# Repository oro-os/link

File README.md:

<div align="center">
	
</div>

# Oro Link

This is the Oro Link project, a set of custom PCBs, firmware, and server
infrastructure for the testing of the Oro Operating System via CI/CD pipelines.

The link is a physical board that interfaces with the ports and headers
of supported computers, devices, and boards, and runs firmware to obtain builds of
the Oro kernel and associated modules to send to the System Under Test (SUT)
for automated testing and reporting.

The Oro Link allows contributors to the Oro project direct access - via
pull requests - to test changes directly on real hardware
alongside emulated environments, allowing for changes to be tested
against niche or problematic hardware configurations.

## Project Layout

All PCBs are located in `pcb/`, where all of the server infrastructure and firmware for the PCBs
is located in `firmware/` since it's a workspace with some local dependencies (e.g. the protocol
spoken between the boards and the CI/CD daemon).

# License

<div align="center">
	
</div>

Part of the Oro Operating System project.

The Oro Link is released to the public, WARRANTY FREE
and provided AS IS. The Oro project and its contributors are NOT
responsible for any damages caused by the purchase, assembly, or operation
of the device, under any circumstances.

The Oro Link's PCB and associated custom footprints are released
under the [MIT License](LICENSE).

Unless otherwise specified, all Oro Link firmware (software code)
and all other materials are licensed under the same license.

Firmware dependencies are under their respective licenses.

The _Enter Command_ font used in part for text display is released CC-BY-4.0
by [Font End Dev (jeti)](https://fontenddev.com).

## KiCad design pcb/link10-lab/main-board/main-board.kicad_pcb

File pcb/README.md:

# Oro Link PCBs

The Oro Link PCBs are custom boards meant to interface with the
CI/CD daemon, which itself works with (at the moment, solely) GitHub
Actions runners that it manages.

These PCBs are open source and licensed under the license found in the
root of this repository.

All PCBs are designed in KiCad 7, with some technical sketches
designed in FreeCad.

There are some "legacy" PCBs here that haven't been converted to
self-standing projects (that use the `.lib/` folder). Further,
some of these PCBs are specific to individual rigs and may not
be interesting to most people.

## `link-rpi-base`

This is the base board for Raspberry Pi test rigs. It hosts
the microcontroller, network interface, etc. as well as a
board-to-board connector that interfaces with one of the
daughter boards (R-Pi version specific).

## `link-x86-obt`

> **NOTE:** This project file is a _legacy_ PCB that hasn't
> been converted to use the common components/footprints library
> in `.lib/`. You will be able to view the schematic and layout,
> but changes are more difficult to make and manage. Due to this,
> PRs that include changes to this PCB might take longer to merge.

This is the main board for testing x86/x86_64 machines using
the Oro Link CI/CD pipeline. Kernel builds are booted over PXE,
and communication is done primarily through the serial ports.

The board's form factor is designed to be mounted to the front
of an [Open Bench Table](https://openbenchtable.com/) - hence
`*-obt`.

As such, the board has two ethernet connections - one for communication
with the SUT, and the other for communication with the Link daemon.

Please see the [firmware directory](../firmware/link-firmware-x86)
for a block diagram and further explanations.

## `rj45-inverter-h410mb`

> **NOTE:** This is a rig-specific board that is likely uninteresting
> to you. It's meant to fit and cater to a very specific hardware
> configuration that most likely won't match yours. As such, this PCB
> is not required to operate a Link test rig, and probably won't
> be of use unless you match the test rig's build exactly.

> **NOTE:** This project file is a _legacy_ PCB that hasn't
> been converted to use the common components/footprints library
> in `.lib/`. You will be able to view the schematic and layout,
> but changes are more difficult to make and manage. Due to this,
> PRs that include changes to this PCB might take longer to merge.

This board has a board-mounted RJ-45 plug (_not_ socket - THT
mounted plugs were really tricky to find!) that is wired same-side
to an RJ-45 port. It's used on one of the x86 test rigs to keep the
left side of the OBT setup flush, without having an ethernet cable
poking out to the left and causing clearance issues.

## `vga-display-card-h410mb`

> **NOTE:** This is a rig-specific board that is likely uninteresting
> to you. It's meant to fit and cater to a very specific hardware
> configuration that most likely won't match yours. As such, this PCB
> is not required to operate a Link test rig, and probably won't
> be of use unless you match the test rig's build exactly.

> **NOTE:** This project file is a _legacy_ PCB that hasn't
> been converted to use the common components/footprints library
> in `.lib/`. You will be able to view the schematic and layout,
> but changes are more difficult to make and manage. Due to this,
> PRs that include changes to this PCB might take longer to merge.

This board provides power to a [VGA display](https://www.amazon.de/-/en/gp/product/B09ZDK5DMT/ref=ppx_yo_dt_b_search_asin_title?ie=UTF8&psc=1) via a PCIe x1
port on the motherboard. It also doubles as a VGA port mount
for the graphics card (which uses a cable to interface between the
card and the port), which further allows the left side of the OBT
to remain flush.

If you're interested in using the VGA display linked above, I
recommend to take it apart, desolder the transducer (beeper)
in the top corner of the board, and replace it with a resistor,
lest you go insane.

# Making a new board

If you want to add a project here, you'll need to do a few things:

1. Make the folder here. Use kebab-case, such as `link-rpi-2` instead of
   `LinkRpi2`.
2. Open KiCad and create the project in the folder. Uncheck the box that
   asks if you want to create a project folder. Preferably, name the project
   using TitleCase, such as `LinkRpi2`.
3. From any **non-legacy** project (see the above list), copy `fp-lib-table`
   and `sym-lib-table` into the new project's directory. **Restart KiCad.**
4. In both the schematic and the PCB layout, go to _File > Page Setup..._
   and change the worksheet to `${KIPRJMOD}/../.lib/Oro.kicad_wks`.
5. If you're using common sheets to re-use some of the modular schematics
   from other boards, **always use relative paths**
   (e.g. `${KIPRJMOD}/../.lib/<something>`).

If you're adding a component, it is **highly** recommended to add it from
[Ultra Librarian](https://ultralibrarian.com).

Symbols and footprints must be added to `.lib/Oro.kicad_sym` and `.lib/Oro.pretty/`,
respectively. STEP models should be placed in `.lib/step` and properly linked up
from within the footprint (usually requires manually editing the footprint after
loading it into `Oro.pretty/`).

Further, make sure to update the footprint ID in the symbol after moving it into the
Oro library.

Most importantly, **you must make sure all common fields are populated and accurate**.
These are fields found on other symbols, the names of which must match **exactly**.
For example, Mouser ID, Mfr. ID, etc.

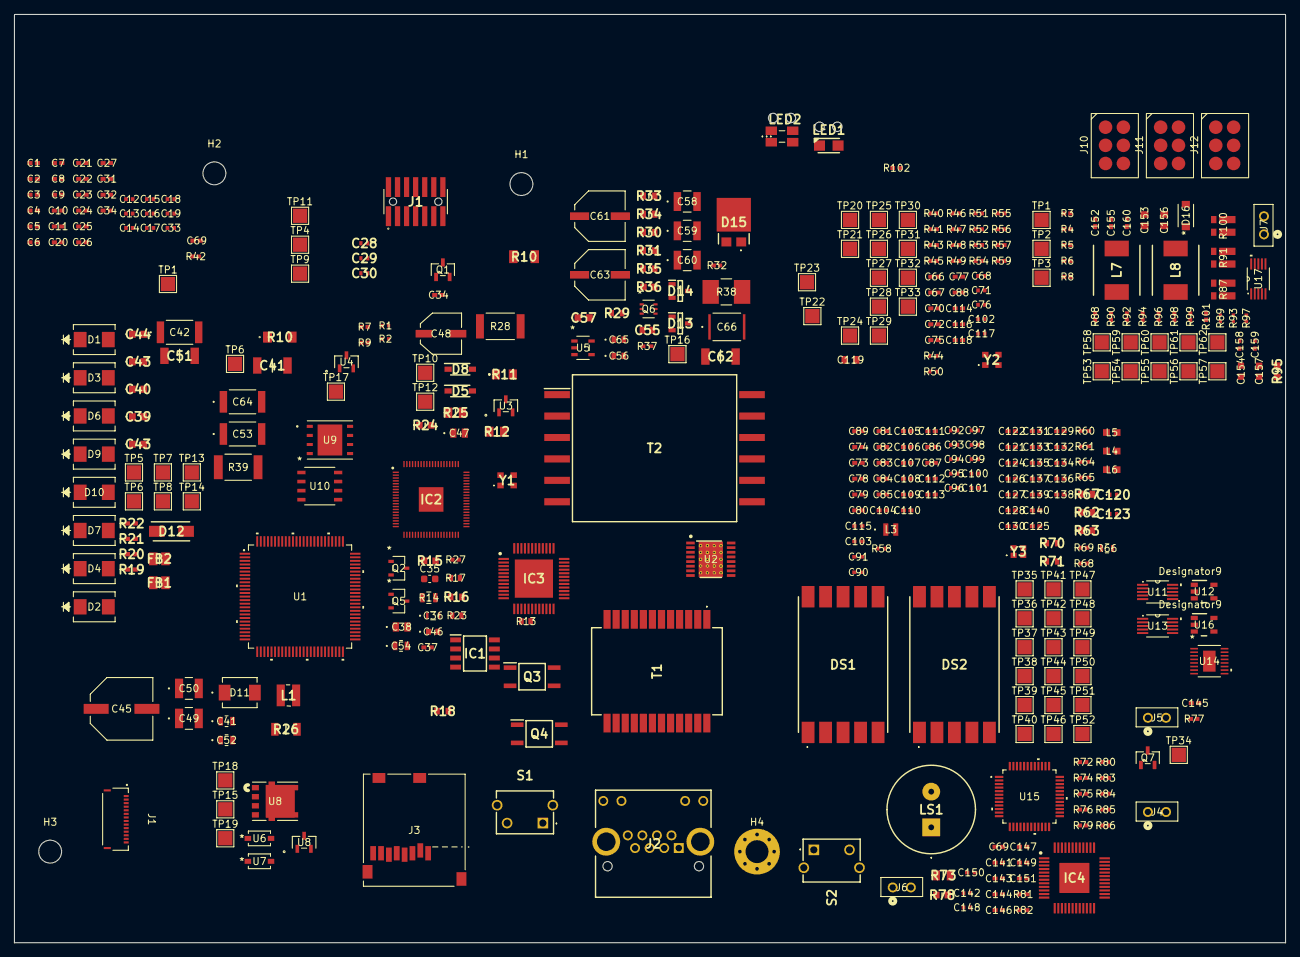
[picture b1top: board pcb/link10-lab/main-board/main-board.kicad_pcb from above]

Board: 2 copper layers, 178.0 x 130.0 mm, 415 parts (0 on the bottom side), 212 nets, no tracks yet.

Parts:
C1, C2, C3: 2.2u; OP_0001G
C4, C5, C6, C7, C8, C9, C10, C11, C32, C34, C34#2, C37, C67, C69, C69#2, C70, C73, C74, C75, C78, C79, C80, C81, C82, C83, C84, C85, C86, C87, C88, C89, C116, C121, C122, C124, C125, C127, C128, C131, C132, C133, C134, C136, C137, C138, C139, C140, C141, C144, C145, C146, C147, C151, C152, C155, C160: 0.1u; OP_0001Y
C12, C13, C14, C15, C16, C17, C18, C19, C33, C68, C71, C76, C92, C93, C94, C95, C96, C97, C98, C99, C100, C101, C102, C117, C142, C148: 0.01u; OP_0000F
C20, C21, C22, C23, C24, C25, C26, C27, C31, C66, C72, C77, C104, C105, C106, C107, C108, C109, C110, C111, C112, C113, C114, C118, C126, C129, C130, C135, C143, C149: 1u; OP_0001R
C28, C29, C30, C90, C91, C103, C115, C150, C158, C159: 4.7u; OP_00014
C35: DNP; C_0603_1608Metric
C36: 0.022uF 50V; OP_00069
C38: 1uF; OP_0005T
C39, C40, C43#2, C44: 10nF 150V; OP_0005C
C41: 1000pF >=2kV; OP_0000R
C41#2, C52, C54: 0.1uF 100V; OP_0005M
C42, C64: 1000pF Y2; OP_0006V
C43: 10nF >=150V; OP_0005C
C45: 47uF 63V; OP_0005N
C46: 330pF; OP_00068
C47: 1uF 25V; OP_0005T
C48: 22uF 25V; OP_0005V
C49, C50: 1uF 100V X7R 1210; OP_0005L
C51: 1000pF 2kV; OP_0000R
C53: 2200pF Y2; OP_0006U
C55: 470pF; OP_0006Q
C56, C65: 1uF; OP_00001
C57: 0.01u; OP_0005C
C58, C59, C60: 47uF; OP_0006G
C61, C63: 330uF; OP_0006H
C62: 1000pF; OP_0000R
C66#2: 2200pF 2kV; OP_0006T
C119, C153, C156: 10u; OP_0001M
C120, C123: 12pF 1% C0G; OP_00071
C154, C157: 22u; OP_00015
D1, D2, D3, D4, D6, D7, D9, D10: B2100-13-F; OP_0005E
D5, D8: 1N4148W; OP_0005S
D11: MURS120T3G; OP_0005P
D12: 824500581 OR SMAJ58A; OP_0005G
D13, D14: BAT54; OP_0006I
D15: SS8P4C-M3_87A; OP_0006E
D16: SMF6V0A-M3-08; OP_0003V
DS1, DS2: HDSM-531W; OP_00077
FB1, FB2: 500R >=1.5A; OP_0005F
H1, H2, H3: MountingHole; MountingHole_3.2mm_M3
H4: MountingHole_Pad; MountingHole_3.2mm_M3_Pad_Via
H5, H6: SLP3-200-100-F; OP_0007E
IC1: SI4848DY-T1-E3; OP_0005R
IC2: SC1510-A4; OP_00050
IC3: W6300-L; OP_00056
IC4: IS31FL3236A-TQLS4-TR; OP_0001Q
J1: 5034801400; OP_00052
J1#2: FTSH-107-01-L-DV-K-A-TR; OP_0005A
J2: 1149867; OP_00053
J3: MEM2061-01-188-00-A; OP_0001X
J4, J5, J6, J7: TSW-102-07-T-S; OP_00079
J10, J11, J12: CPG-81-TH-B-Pads; CPG-81-TH-B-Landing
L1: LPS3015-332MRC; OP_0005I
L3: AOTA-B201610S3R3-101-T; OP_00073
L4, L5, L6: BLM18PG221SN1D; OP_0000Y
L7, L8: 2.2u; OP_0007C
LED1: CLM3C-WKW-CXAYA453; OP_00016
LED2: 150120M173000; OP_00006
LS1: CPT-1206-3TH-T; OP_00078
Q1, Q7: PMV20ENR; OP_0001Z
Q2, Q5: SI2304DDS-T1-BE3; OP_00063
Q3, Q4: HCPL-181-06AE; OP_00062
Q6: 2N7002DW; OP_0006D
R1, R2, R81, R82, R102: 4.7K; OP_0001C
R3, R4, R5, R6, R7, R8, R9, R27, R32, R40, R41, R42, R43, R45, R46, R47, R48, R49, R51, R52, R53, R54, R55, R56, R57, R59, R68, R69, R72, R74, R75, R76, R77, R79, R80, R83, R84, R85, R86, R88, R90, R92, R94, R96, R98, R99, R101: 10K; OP_00021
R10: ~1M ANTI-SURGE; OP_0005D
R10#2: 24.9K 1% 1/4W 150V; OP_0005H
R11: 63R4 1/10W 1%; OP_0005W
R12: 34K 1%; OP_0005X
R13: 3.65K 1%; OP_0006A
R14: 1K; OP_0003D
R15, R78, R95: 100K; OP_00066
R16: 33.2K 1%; OP_00065
R17: 549K 1%; OP_00064
R18: 475K 1/16W 1%; OP_0005Q
R19, R20, R21, R22: 75R 1%; OP_0002Z
R23: 332R; OP_00067
R24: 43R2 1%; OP_0005Y
R25: 10R 0805; OP_0005U
R26: 15K 0.25W; OP_0005O
R28: 0.1R 1% 1/2W; OP_00060
R29, R70, R71: 604R; OP_0006K
R30: 4R7; OP_0006O
R31: 4.99K; OP_0006P
R33: 41.2K; OP_0006J
R34: 13.7K; OP_0006M
R35: 20K; OP_0006R
R36: 30.1K; OP_0006S
R37, R60, R61, R64, R65: 49R9; OP_00023
R38: 10R 1W; OP_0006N
R39: 1-2.2M 2kV; OP_0006W
R44, R50: 22R-33R; OP_00022
R58: 33R; OP_00022
R62: 1M; OP_00072
R63: 0R; OP_0004Y
R66: 12K 1%; OP_0006Y
R67: 300R 1%; OP_0006Z
R73: 470R; OP_00031
R87, R91, R100: 2m; OP_0002G
R89, R93: 45.3K; OP_0007A
R97: 249R; OP_0007B
S1, S2: MJTP1129B; OP_0005B
T1: 749022011; OP_00058
T2: NA5730-ALD; OP_0005J
TP1: STM_BOOT1; TestPoint_Pad_2.0x2.0mm
TP1#2: CHASSIS; TestPoint_Pad_2.0x2.0mm
TP2: STM_BOOT0; TestPoint_Pad_2.0x2.0mm
TP3: STM_NRST; TestPoint_Pad_2.0x2.0mm
TP4: POE_CS; TestPoint_Pad_2.0x2.0mm
TP5: PAIR12; TestPoint_Pad_2.0x2.0mm
TP6: GND; TestPoint_Pad_2.0x2.0mm
TP6#2: PAIR36; TestPoint_Pad_2.0x2.0mm
TP7: PAIR45; TestPoint_Pad_2.0x2.0mm
TP8: PAIR78; TestPoint_Pad_2.0x2.0mm
TP9: POE_GATE; TestPoint_Pad_2.0x2.0mm
TP10: POE_VC; TestPoint_Pad_2.0x2.0mm
TP11: POE_PRIM_SWITCH_WAV; TestPoint_Pad_2.0x2.0mm
TP12: POE_AGND; TestPoint_Pad_2.0x2.0mm
TP13: POE_VDD; TestPoint_Pad_2.0x2.0mm
TP14: POE_VSS; TestPoint_Pad_2.0x2.0mm
TP15: POE_SDRN; TestPoint_Pad_2.0x2.0mm
TP16: POE_LOOP; TestPoint_Pad_2.0x2.0mm
TP17: POE_CHASSIS; TestPoint_Pad_2.0x2.0mm
TP18: POE_+5V; TestPoint_Pad_2.0x2.0mm
TP19: POE_GND; TestPoint_Pad_2.0x2.0mm
TP20: RP_QSS0; TestPoint_Pad_2.0x2.0mm
TP21: RP_QD1; TestPoint_Pad_2.0x2.0mm
TP22: RP_QD2; TestPoint_Pad_2.0x2.0mm
TP23: RP_QD0; TestPoint_Pad_2.0x2.0mm
TP24: RP_QCLK; TestPoint_Pad_2.0x2.0mm
TP25: RP_QD3; TestPoint_Pad_2.0x2.0mm
TP26: RP_QSS1; TestPoint_Pad_2.0x2.0mm
TP27: SD_CLK; TestPoint_Pad_2.0x2.0mm
TP28: SD_CMD; TestPoint_Pad_2.0x2.0mm
TP29: SD_DAT0; TestPoint_Pad_2.0x2.0mm
TP30: SD_DAT1; TestPoint_Pad_2.0x2.0mm
TP31: SD_DAT2; TestPoint_Pad_2.0x2.0mm
TP32: SD_DAT3; TestPoint_Pad_2.0x2.0mm
TP33: SD_DETECT; TestPoint_Pad_2.0x2.0mm
TP34: RP_NRST; TestPoint_Pad_2.0x2.0mm
TP35: BB_SCL; TestPoint_Pad_2.0x2.0mm
TP36: BB_SDA; TestPoint_Pad_2.0x2.0mm
TP37: DGT_~{RST}; TestPoint_Pad_2.0x2.0mm
TP38: DGT_~{SENSE}; TestPoint_Pad_2.0x2.0mm
TP39: BB_STM_~{INT}; TestPoint_Pad_2.0x2.0mm
TP40: BB_~{RST}; TestPoint_Pad_2.0x2.0mm
TP41: BB_SYS_~{RST}; TestPoint_Pad_2.0x2.0mm
TP42: BB_SPK; TestPoint_Pad_2.0x2.0mm
TP43: DGT_E0; TestPoint_Pad_2.0x2.0mm
TP44: DGT_E1; TestPoint_Pad_2.0x2.0mm
TP45: DGT_E2; TestPoint_Pad_2.0x2.0mm
TP46: DGT_E3; TestPoint_Pad_2.0x2.0mm
TP47: RP_E0; TestPoint_Pad_2.0x2.0mm
TP48: RP_E1; TestPoint_Pad_2.0x2.0mm
TP49: RP_E2; TestPoint_Pad_2.0x2.0mm
TP50: RP_E3; TestPoint_Pad_2.0x2.0mm
TP51: BB_LEDCTL_EN; TestPoint_Pad_2.0x2.0mm
TP52: MASTER_LIGHT_EN; TestPoint_Pad_2.0x2.0mm
TP53: BB_PWR_WARN; TestPoint_Pad_2.0x2.0mm
TP54: MASTER_PWR_WARN; TestPoint_Pad_2.0x2.0mm
TP55: STM_PWR_EN; TestPoint_Pad_2.0x2.0mm
TP56: DGT_PWR_EN; TestPoint_Pad_2.0x2.0mm
TP57: DGT_PWR_ALARM; TestPoint_Pad_2.0x2.0mm
TP58: DGT_PWR_WARN; TestPoint_Pad_2.0x2.0mm
TP59: 5V_BASE; TestPoint_Pad_2.0x2.0mm
TP60: 3V3_BASE; TestPoint_Pad_2.0x2.0mm
TP61: 3V3_STM; TestPoint_Pad_2.0x2.0mm
TP62: 5V_DGT; TestPoint_Pad_2.0x2.0mm
U1: STM32F479VGT6; OP_00028
U2: TPS23751PWP; OP_00057
U3, U4, U8: MMBT3906LT1G; OP_0005Z
U5: TLV431ASNT1G; OP_0006L
U6, U7: MBR0530T1G; OP_0006B
U8#2: NTMFS4C55NT1G; OP_0006C
U9: W25Q128JVPIM; OP_00054
U10: APS6404L-3SQR-SN; OP_00055
U11, U13, U17: INA226AIDGSR; OP_0001O
U12, U16: TLV62569DBVR; OP_00075
U14: LTC4415EMSE-PBF; OP_0004S
U15: STM32C031C4T6; OP_00076
Y1, Y2: ECS-2520SMV-240-FP-TR; OP_0001E
Y3: 25MHz CL=10pF; OP_00070

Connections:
+3V3_BASE: C144.2, C147.1, C148.1, C149.1, C150.1, C152.1, C154.1, C155.1, C160.1, L7.2, R72.2, R76.2, R79.1, R81.1, R82.1, R83.2, R84.2, R88.2, R89.1, R92.2, R96.2, R98.2, R99.2, R101.2, TP60.1 (1_1), U11.6 (VS), U13.2 (A0), U13.6 (VS), U15.5 (VREF+), U15.6 (VDD/VDDA), U17.1 (A1), U17.6 (VS)
+3V3_STM: C4.1, C5.1, C6.1, C7.1, C8.1, C9.1, C10.1, C11.1, C12.1, C13.1, C14.1, C15.1, C16.1, C17.1, C18.1, C19.1, C20.1, C21.1, C22.1, C23.1, C24.1, C25.1, C26.1, C27.1, C28.1, C29.1, C30.1, C31.2, C32.2, C33.2, C66.2, C67.2, C68.2, C70.1, C71.1, C72.1, C75.1, C76.1, C77.1, C78.1, C79.1, C80.1, C81.1, C82.1, C83.1, C84.1, C85.1, C86.1, C87.1, C88.1, C92.1, C93.1, C94.1, C95.1, C96.1, C97.1, C98.1, C99.1, C100.1, C101.1, C102.1, C103.2, C104.1, C105.1, C106.1, C107.1, C108.1, C109.1, C110.1, C111.1, C112.1, C113.1, C114.1, C116.1, C117.1, C118.1, C119.1, C126.2, C127.2, C128.2, C157.1, IC2.5 (IOVDD_1), IC2.15 (IOVDD_2), IC2.24 (IOVDD_3), IC2.29 (IOVDD_4), IC2.41 (IOVDD_5), IC2.50 (IOVDD_6), IC2.59 (ADC_AVDD), IC2.60 (IOVDD_7), IC2.64 (VREG_VIN), IC2.68 (USB_OTP_VDD), IC2.69 (QSPI_IOVDD), IC2.76 (IOVDD_8), IC3.10 (3V3D_1), IC3.24 (3V3D_2), IC3.36 (3V3D_3), J3.P4 (VDD), L5.2, L8.2, R1.1, R2.1, R3.2, R5.2, R6.2, R7.2, R9.2, R40.2, R41.2, R42.2, R43.1, R45.1, R46.1, R47.1, R48.1, R49.1, R51.2, R52.2, R53.2, R54.2, R55.2, R56.2, R57.2, R58.1, R59.2, R68.2, R70.2, R71.2, R77.2, R86.1, R93.1, TP61.1 (1_1), U1.3 (VBAT), U1.8 (VDD), U1.17 (VREF+), U1.18 (VDDA), U1.24 (VDD), U1.45 (VDD), U1.55 (VDDDSI), U1.65 (VDDUSB), U1.77 (VDD), U1.100 (VDD), U9.8 (VCC), U10.8 (VDD), Y1.4 (VDD), Y2.4 (VDD)
+5V: C63.1, C65.1, C158.1, D16.1, LED1.1 (A), R35.2, R36.2, R37.1, R87.1, R91.1, TP18.1 (1_1), U14.1 (IN1), U14.2 (IN1), U14.6 (*EN2)
+5V_BASE: C69#2.1, C142.1, C143.1, C153.1, DS1.3 (COMMON_ANODE_1), DS1.8 (COMMON_ANODE_2), DS2.3 (COMMON_ANODE_1), DS2.8 (COMMON_ANODE_2), IC4.41 (VCC), LED2.2 (A_G), R75.1, R87.4, TP59.1 (1_1), U11.8 (VBUS), U16.1 (EN), U16.4 (VIN)
+5V_DGT: R100.4, TP62.1 (1_1), U17.8 (VBUS)
/Baseboard/BB_PWR_WARN: R88.1, TP53.1 (1_1), U11.3 (ALERT), U15.8 (PF0-OSC_IN)
/Baseboard/DGT_ERR.E0: TP43.1 (1_1), U15.20 (PB1)
/Baseboard/DGT_ERR.E1: TP44.1 (1_1), U15.21 (PB2)
/Baseboard/DGT_ERR.E2: TP45.1 (1_1), U15.22 (PB10)
/Baseboard/DGT_ERR.E3: TP46.1 (1_1), U15.23 (PB11)
/Baseboard/DGT_PWR_ALARM: R99.1, TP57.1 (1_1), U14.13 (*WARN1), U15.29 (PA9)
/Baseboard/DGT_PWR_EN: R98.1, TP56.1 (1_1), U14.3 (EN1), U15.28 (PA8)
/Baseboard/DGT_PWR_WARN: R101.1, TP58.1 (1_1), U15.31 (PC7), U17.3 (ALERT)
/Baseboard/DGT_~RST: R78.2, TP37.1 (1_1), U15.27 (PB15)
/Baseboard/DGT_~SENSE: R83.1, TP38.1 (1_1), U15.37 (PA15)
/Baseboard/ERR_B: IC4.34 (OUT32), LED2.1 (K_B)
/Baseboard/ERR_G: IC4.35 (OUT33), LED2.3 (K_G)
/Baseboard/ERR_R: IC4.36 (OUT34), LED2.4 (K_R)
/Baseboard/I2C1.SCL: IC4.46 (SCL), R82.2, TP35.1 (1_1), U11.5 (SCL), U13.5 (SCL), U15.47 (PB8), U17.5 (SCL)
/Baseboard/I2C1.SDA: IC4.45 (SDA), R81.2, TP36.1 (1_1), U11.4 (SDA), U13.4 (SDA), U15.48 (PB9), U17.4 (SDA)
/Baseboard/LEDCTL_EN: IC4.39 (SDB), R74.1, TP51.1 (1_1), U15.4 (PF3)
/Baseboard/MASTER_LIGHT_EN: TP52.1 (1_1), U15.46 (PB7)
/Baseboard/MASTER_PWR_EN: J7.1, R95.1, TP55.1 (1_1), U12.1 (EN), U15.40 (PD2)
/Baseboard/MASTER_PWR_WARN: R92.1, TP54.1 (1_1), U13.3 (ALERT), U15.26 (PB14)
/Baseboard/O10: DS2.1 (CATHODE_E), IC4.9 (OUT10)
/Baseboard/O11: DS2.2 (CATHODE_D), IC4.10 (OUT11)
/Baseboard/O12: DS2.4 (CATHODE_C), IC4.11 (OUT12)
/Baseboard/O13: DS2.6 (CATHODE_B), IC4.12 (OUT13)
/Baseboard/O14: DS2.7 (CATHODE_A), IC4.13 (OUT14)
/Baseboard/O15: DS2.9 (CATHODE_F), IC4.14 (OUT15)
/Baseboard/O16: DS2.10 (CATHODE_G), IC4.15 (OUT16)
/Baseboard/O17: DS1.1 (CATHODE_E), IC4.16 (OUT17)
/Baseboard/O18: DS1.2 (CATHODE_D), IC4.17 (OUT18)
/Baseboard/O19: DS1.4 (CATHODE_C), IC4.20 (OUT19)
/Baseboard/O20: DS1.10 (CATHODE_G), IC4.21 (OUT20)
/Baseboard/O21: DS1.9 (CATHODE_F), IC4.22 (OUT21)
/Baseboard/O22: DS1.7 (CATHODE_A), IC4.23 (OUT22)
/Baseboard/O23: DS1.6 (CATHODE_B), IC4.24 (OUT23)
/Baseboard/RP_ERR.E0: IC2.40 (GPIO32), TP47.1 (1_1), U15.42 (PB3)
/Baseboard/RP_ERR.E1: IC2.39 (GPIO31), TP48.1 (1_1), U15.43 (PB4)
/Baseboard/RP_ERR.E2: IC2.38 (GPIO30), TP49.1 (1_1), U15.44 (PB5)
/Baseboard/RP_ERR.E3: IC2.37 (GPIO29), TP50.1 (1_1), U15.45 (PB6)
/Baseboard/RP_RST: Q7.1 (G), R77.1, U15.32 (PA10)
/Baseboard/SPI1.CLK: U1.37 (PE12), U15.16 (PA5)
/Baseboard/SPI1.MISO: U1.38 (PE13), U15.17 (PA6)
/Baseboard/SPI1.MOSI: U1.39 (PE14), U15.18 (PA7)
/Baseboard/SPI_~CS: R79.2, U15.19 (PB0)
/Baseboard/STM32_RST: Q1.1 (G), R9.1, U15.30 (PC6)
/Baseboard/STM32_~INT: R84.1, TP39.1 (1_1), U15.38 (PD0)
/Baseboard/~RST: C146.2, R76.1, TP40.1 (1_1), U15.10 (PF2-NRST)
/Bridge (RP) + SD/+1V1: C73.2, C74.2, C89.2, C90.2, C91.2, IC2.10 (DVDD_1), IC2.32 (DVDD_2), IC2.51 (DVDD_3), IC2.65 (VREG_FB), L3.1 (-)
/Bridge (RP) + SD/+3V3A: C115.2, IC2.61 (VREG_AVDD), R58.2
/Bridge (RP) + SD/AGND: C69.1, S1.2 (NO)
/Bridge (RP) + SD/DGT_SDIO.CMD: IC2.43 (GPIO34), R43.2
/Bridge (RP) + SD/DGT_SDIO.D0: IC2.44 (GPIO35), R45.2
/Bridge (RP) + SD/DGT_SDIO.D1: IC2.45 (GPIO36), R46.2
/Bridge (RP) + SD/DGT_SDIO.D2: IC2.46 (GPIO37), R47.2
/Bridge (RP) + SD/DGT_SDIO.D3: IC2.47 (GPIO38), R48.2
/Bridge (RP) + SD/DGT_SDIO_~INT: IC2.48 (GPIO39), R49.2
/Bridge (RP) + SD/ETH_QPI.CLK: IC2.79 (GPIO2), IC3.30 (SCLK)
/Bridge (RP) + SD/ETH_QPI.CS: IC2.80 (GPIO3), IC3.29 (CSN)
/Bridge (RP) + SD/ETH_QPI.D0: IC2.1 (GPIO4), IC3.32 (QD0)
/Bridge (RP) + SD/ETH_QPI.D1: IC2.2 (GPIO5), IC3.33 (QD1)
/Bridge (RP) + SD/ETH_QPI.D2: IC2.3 (GPIO6), IC3.34 (QD2)
/Bridge (RP) + SD/ETH_QPI.D3: IC2.4 (GPIO7), IC3.35 (QD3)
/Bridge (RP) + SD/ETH_~INT: IC2.6 (GPIO8), IC3.45 (INTN), R68.1
/Bridge (RP) + SD/ETH_~RST: IC2.7 (GPIO9), IC3.46 (RSTN), R69.2
/Bridge (RP) + SD/SD.CLK: IC2.18 (GPIO18), R50.1, TP27.1 (1_1)
/Bridge (RP) + SD/SD.CMD/MOSI: IC2.19 (GPIO19), J3.P3 (CMD), R53.1, TP28.1 (1_1)
/Bridge (RP) + SD/SD.DAT0/MISO: IC2.20 (GPIO20), J3.P7 (DAT0), R54.1, TP29.1 (1_1)
/Bridge (RP) + SD/SD.DAT1: IC2.21 (GPIO21), J3.P8 (DAT1), R55.1, TP30.1 (1_1)
/Bridge (RP) + SD/SD.DAT2: IC2.22 (GPIO22), J3.P1 (DAT2), R56.1, TP31.1 (1_1)
/Bridge (RP) + SD/SD.DAT3/CS: IC2.23 (GPIO23), J3.P2 (CD/DAT3), R57.1, TP32.1 (1_1)
/Bridge (RP) + SD/SD_DETECT: IC2.17 (GPIO17), J3.9 (CARD_DETECT), J3.10 (CARD_DETECT), R59.1, TP33.1 (1_1)
/Bridge (RP) + SD/STM32_~INT_READY: IC2.8 (GPIO10), R40.1
/Bridge (RP) + SD/STM_SPI.CLK: IC2.13 (GPIO14), U1.81 (PC10)
/Bridge (RP) + SD/STM_SPI.MISO: IC2.14 (GPIO15), U1.82 (PC11)
/Bridge (RP) + SD/STM_SPI.MOSI: IC2.11 (GPIO12), U1.83 (PC12)
/Bridge (RP) + SD/STM_SPI.NSS: IC2.12 (GPIO13), R5.1, U1.25 (PA4)
/Bridge (RP) + SD/VREG_LX: IC2.63 (VREG_LX), L3.2 (+)
/Bridge (RP) + SD/~RST_DIRECT: C145.2, IC2.35 (RUN), J5.1, R42.1, TP34.1 (1_1)
/CHASSIS: C42.1, C64.1, H4.1 (1_1), J2.MH1, J2.MH2, R39.2, TP17.1 (1_1)
/Ethernet Port + PoE/AGND: C37.1, C38.1, C41#2.2, C45.2, C46.1, C47.1, C48.2, C49.1, C50.1, C53.1, C66#2.1, Q2.2 (S), Q4.3, R12.2, R16.2, R28.1, T2.6 (BIAS_2), TP12.1 (1_1), U2.4 (APD), U2.14 (ARTN), U2.15 (RTN), U3.3 (C)
/Ethernet Port + PoE/ETH.RX+: IC3.5 (RXIP), R60.2, T1.5 (D-_3)
/Ethernet Port + PoE/ETH.RX-: IC3.4 (RXIN), R61.2, T1.6 (D-_4)
/Ethernet Port + PoE/ETH.TX+: IC3.2 (TXOP), R64.2, T1.2 (D-_1)
/Ethernet Port + PoE/ETH.TX-: IC3.1 (TXON), R65.2, T1.3 (D-_2)
/Ethernet Port + PoE/ETH.TXCT: C122.2, C130.2, C131.2, C133.2, C135.2, C137.2, C139.2, C140.2, IC3.7 (3V3A_1), IC3.14 (3V3A_2), L5.1, T1.1 (TD_1), T1.4 (TD_2)
/Ethernet Port + PoE/GND: C66#2.2, U8.3 (C)
/Ethernet Port + PoE/LED_G+: J2.10 (G_A), R70.1
/Ethernet Port + PoE/LED_G-: IC3.19 (LNKN), J2.9 (G_C)
/Ethernet Port + PoE/LED_Y+: J2.12 (Y_A), R71.1
/Ethernet Port + PoE/LED_Y-: IC3.22 (ACTN), J2.11 (Y_C)
/Ethernet Port + PoE/POE_VDD: C41#2.1, C43.2, C45.1, C54.1, D12.1 (K), FB1.1, L1.1, R10#2.2, R18.1, TP13.1 (1_1), U2.1 (VDD)
/Ethernet Port + PoE/POE_VSS: C43.1, C54.2, D12.2 (A), FB2.1, R11.2, TP14.1 (1_1), U2.16 (VSS), U2.17 (PAD)
/Ethernet/1V2O: C129.2, IC3.13 (1V2O), L4.1, L6.2
/Ethernet/+1V2: C132.2, C134.2, C136.2, C138.2, IC3.9 (1V2D_1), IC3.18 (1V2D_2), IC3.31 (1V2D_3), IC3.47 (1V2D_4), L6.1
/Ethernet/+1V2A: C125.2, IC3.3 (1V2A_1), IC3.16 (1V2A_2), L4.2
/Ethernet/XI: C120.2, IC3.11 (XSCI), R62.2, Y3.1 (IN/OUT)
/Ethernet/XO: IC3.12 (XSCO), R62.1, R63.2
/GND: C41.2, R10.1, TP6.1 (1_1)
/Microcontroller/BOOT0: R8.2, TP2.1 (1_1), U1.97 (BOOT0)
/Microcontroller/BOOT1: R4.2, TP1.1 (1_1), U1.31 (PB2)
/Microcontroller/DGT_SPI_~CSE: R6.1, U1.15 (PC3)
/Microcontroller/I2C1.SCL: R1.2, U1.98 (PB8)
/Microcontroller/I2C1.SDA: R2.2, U1.96 (PB7)
/Microcontroller/SPI2.NSS: R3.1, U1.99 (PB9)
/Microcontroller/~RST_DIRECT: C34.2, J4.1, TP3.1 (1_1), U1.11 (NRST)
/Power/+5V_STM: C156.1, R91.4, U12.4 (VIN), U13.8 (VBUS)
/Power/DGT_SW: C159.1, R100.1, U14.15 (OUT1), U14.16 (OUT1)
CHASSIS: C41.1, R10.2, TP1#2.1 (1_1)
GND: C1.1, C2.1, C3.1, C4.2, C5.2, C6.2, C7.2, C8.2, C9.2, C10.2, C11.2, C12.2, C13.2, C14.2, C15.2, C16.2, C17.2, C18.2, C19.2, C20.2, C21.2, C22.2, C23.2, C24.2, C25.2, C26.2, C27.2, C28.2, C29.2, C30.2, C31.1, C32.1, C33.1, C34.1, C53.2, C56.2, C58.2, C59.2, C60.2, C61.2, C63.2, C64.2, C65.2, C66.1, C67.1, C68.1, C69#2.2, C70.2, C71.2, C72.2, C73.1, C74.1, C75.2, C76.2, C77.2, C78.2, C79.2, C80.2, C81.2, C82.2, C83.2, C84.2, C85.2, C86.2, C87.2, C88.2, C89.1, C90.1, C91.1, C92.2, C93.2, C94.2, C95.2, C96.2, C97.2, C98.2, C99.2, C100.2, C101.2, C102.2, C103.1, C104.2, C105.2, C106.2, C107.2, C108.2, C109.2, C110.2, C111.2, C112.2, C113.2, C114.2, C115.1, C116.2, C117.2, C118.2, C119.2, C120.1, C121.1, C122.1, C123.1, C124.1, C125.1, C126.1, C127.1, C128.1, C129.1, C130.1, C131.1, C132.1, C133.1, C134.1, C135.1, C136.1, C137.1, C138.1, C139.1, C140.1, C141.1, C142.2, C143.2, C144.1, C145.1, C146.1, C147.2, C148.2, C149.2, C150.2, C151.1, C152.2, C153.2, C154.2, C155.2, C156.2, C157.2, C158.2, C159.2, C160.2, D15.1 (A_1), D15.2 (A_2), D16.2, IC2.62 (VREG_PGND), IC2.81 (GND), IC3.6 (GND33A), IC3.15 (GNDA_1), IC3.17 (GND12A), IC3.25 (MOD0), IC3.26 (MOD1), IC3.27 (MOD2), IC3.28 (MOD3), IC3.48 (GNDA_2), IC3.49 (GND), IC4.4 (GND_1), IC4.18 (GND_2), IC4.19 (GND_3), IC4.33 (GND_4), IC4.42 (GND_5), IC4.43 (GND_6), IC4.49 (EP), J3.11 (GROUND), J3.12 (GROUND), J3.P6 (VSS), Q1.2 (S), Q3.3, Q5.3 (D), Q6.1, Q6.4, Q7.2 (S), R4.1, R8.1, R34.1, R38.1, R39.1, R67.1, R69.1, R74.2, R78.1, R80.1, R85.2, R90.2, R94.2, R95.2, R97.1, R102.1, S2.2 (NO), TP19.1 (1_1), U1.2 (VSS), U1.7 (VSS), U1.16 (VSSA), U1.23 (VSS), U1.44 (VSS), U1.59 (VSSDSI), U1.78 (VSS), U4.3 (C), U5.5 (ANODE), U8#2.1 (SOURCE), U8#2.2 (SOURCE), U8#2.3 (SOURCE), U9.4 (GND), U9.9 (EPAD), U10.4 (VSS), U11.1 (A1), U11.2 (A0), U11.7 (GND), U12.2 (GND), U13.1 (A1), U13.7 (GND), U14.5 (CLIM2), U14.7 (IN2), U14.8 (IN2), U14.EPAD (GND), U15.7 (VSS/VSSA), U16.2 (GND), U17.2 (A0), U17.7 (GND), Y1.2 (GND), Y2.2 (GND), Y3.2 (GND_1), Y3.4 (GND_2)
unnamed: C36.1, R14.1
unnamed: C39.1, R19.2
unnamed: C40.1, R20.2
unnamed: C42.2, R19.1, R20.1, R21.1, R22.1
unnamed: C43#2.1, R21.2
unnamed: C44.1, R22.2
unnamed: C51.1, D2.2, D4.2, D7.2, D10.2, FB2.2
unnamed: C51.2, D1.1, D3.1, D6.1, D9.1, FB1.2
unnamed: C62.1, R38.2
unnamed: C121.2, R60.1, R61.1
unnamed: C124.2, R64.1, R65.1
unnamed: D5.2 (A), R25.1
unnamed: C47.2, C48.1, D5.1 (K), R27.1, TP10.1 (1_1), U2.12 (VC)
unnamed: D8.2 (A), R24.2, U3.1 (B)
unnamed: D8.1 (K), IC1.4 (G), U3.2 (E)
unnamed: D11.2 (A), IC1.5 (D_1), IC1.6 (D_2), IC1.7 (D_3), IC1.8 (D_4), T2.1 (PRI_1_1), T2.2 (PRI_2_1), TP11.1 (1_1)
unnamed: C52.2, D11.1 (K), R26.1
unnamed: C57.1, D13.1 (A), Q4.2, U5.3 (CATHODE)
unnamed: C56.1, D13.3 (K), D14.1 (A), R32.1
unnamed: D14.3 (K), R29.2, R32.2, R33.1, R37.2, TP16.1 (1_1)
unnamed: C62.2, D15.3 (K), T2.9 (SEC_1_1), T2.10 (SEC_2_1), TP15.1 (1_1), U8#2.5 (DRAIN)
unnamed: IC1.1 (S_1), IC1.2 (S_2), IC1.3 (S_3), R23.2, R28.2
unnamed: IC2.42 (GPIO33), R44.1
unnamed: IC2.58 (GPIO47_ADC7), R52.1, TP26.1 (1_1), U10.1 (/CE)
unnamed: IC2.71 (QSPI_SCLK), TP24.1 (1_1), U9.6 (CLK), U10.6 (SCLK)
unnamed: IC2.72 (QSPI_SD0), TP23.1 (1_1), U9.5 (DI_(IO0)), U10.5 (SI/SIO[0])
unnamed: IC2.74 (QSPI_SD1), TP21.1 (1_1), U9.2 (DO_(IO1)), U10.2 (SO/SIO[1])
unnamed: IC2.73 (QSPI_SD2), TP22.1 (1_1), U9.3 (/WP_(IO2)), U10.3 (SIO[2])
unnamed: IC2.70 (QSPI_SD3), TP25.1 (1_1), U9.7 (/HOLD_OR_/RESET_(IO3)), U10.7 (SIO[3])
unnamed: IC2.75 (QSPI_SS), R51.1, TP20.1 (1_1), U9.1 (/CS)
unnamed: C69.2, S1.1 (COM)
unnamed: IC2.30 (XIN), Y2.3 (OUTPUT)
unnamed: IC3.8 (RSET_BG), R66.1
unnamed: IC4.40 (AD), R75.2
unnamed: IC4.44 (R_EXT), R80.2
unnamed: J3.P5 (CLK), R50.2
unnamed: J6.1, R73.1
unnamed: J7.2, R96.1
unnamed: LED1.2 (K), R102.2
unnamed: LS1.1 (+), R73.2, TP42.1 (1_1)
unnamed: LS1.2 (-), U15.14 (PA3)
unnamed: J4.2, Q1.3 (D)
unnamed: Q2.3 (D), R17.1
unnamed: Q2.1 (G), Q3.2, U2.7 (SRD)
unnamed: Q3.1, R27.2
unnamed: Q3.4, Q6.2, Q6.5, R36.1
unnamed: Q4.1, R29.1
unnamed: Q5.1 (G), Q6.6, R35.1
unnamed: Q5.2 (S), T2.7 (DRIVE_1)
unnamed: J5.2, Q7.3 (D)
unnamed: R66.2, R67.2
unnamed: C141.2, R72.1, S2.1 (COM), TP41.1 (1_1), U15.1 (PC13)
unnamed: C44.2, D1.2, D2.1, T1.15 (TX_1), TP8.1 (1_1)
unnamed: C43#2.2, D3.2, D4.1, T1.18 (TX_2), TP7.1 (1_1)
unnamed: C40.2, D6.2, D7.1, T1.21 (TX_3), TP6#2.1 (1_1)
unnamed: C39.2, D9.2, D10.1, T1.24 (TX_4), TP5.1 (1_1)
unnamed: J2.8, T1.13 (X-_1)
unnamed: J2.7, T1.14 (X-_2)
unnamed: J2.5, T1.16 (X-_3)
unnamed: J2.4, T1.17 (X-_4)
unnamed: J2.6, T1.19 (X-_5)
unnamed: J2.3, T1.20 (X-_6)
unnamed: J2.2, T1.22 (X-_7)
unnamed: J2.1, T1.23 (X-_8)
unnamed: R25.2, T2.5 (BIAS_1)
unnamed: C55.1, R30.1, R31.1, T2.8 (DRIVE_2)
unnamed: C49.2, C50.2, C52.1, L1.2, R26.2, T2.3 (PRI_1_2), T2.4 (PRI_2_2)
unnamed: C58.1, C59.1, C60.1, C61.1, T2.11 (SEC_1_2), T2.12 (SEC_2_2)
unnamed: U1.9 (PH0), Y1.3 (OUTPUT)
unnamed: C1.2, U1.43 (VCAP1)
unnamed: C2.2, U1.76 (VCAP2)
unnamed: C3.2, U1.56 (VCAPDSI), U1.62 (VDD12DSI)
unnamed: R11.1, U2.3 (CLS)
unnamed: C46.2, R18.2, R23.1, TP4.1 (1_1), U2.11 (CS)
unnamed: C35.2, C36.2, Q4.4, R13.1, U2.8 (CTL)
unnamed: R10#2.1, U2.2 (DEN)
unnamed: R24.1, TP9.1 (1_1), U2.13 (GATE)
unnamed: R12.1, U2.5 (RT)
unnamed: C37.2, R15.1, R16.1, R17.2, U2.9 (SRT)
unnamed: C35.1, C38.2, R13.2, R14.2, R15.2, U2.10 (VB)
unnamed: C55.2, R31.2, U4.1 (B), U7.2 (ANODE)
unnamed: Q6.3, U4.2 (E), U6.1 (CATHODE), U7.1 (CATHODE), U8#2.4 (GATE)
unnamed: C57.2, R33.2, R34.2, U5.4 (REFERENCE)
unnamed: R30.2, U6.2 (ANODE)
unnamed: R87.2, U11.10 (VIN+)
unnamed: R87.3, U11.9 (VIN-)
unnamed: R93.2, R94.1, U12.5 (FB)
unnamed: L8.1, U12.3 (SW)
unnamed: R91.2, U13.10 (VIN+)
unnamed: R91.3, U13.9 (VIN-)
unnamed: R97.2, U14.4 (CLIM1)
unnamed: J6.2, U15.11 (PA0)
unnamed: C151.2, R85.1, R86.2, U15.15 (PA4)
unnamed: R89.2, R90.1, U16.5 (FB)
unnamed: L7.1, U16.3 (SW)
unnamed: R100.2, U17.10 (VIN+)
unnamed: R100.3, U17.9 (VIN-)
unnamed: R7.1, Y1.1 (TRI-STATE)
unnamed: R41.1, Y2.1 (TRI-STATE)
unnamed: C123.2, R63.1, Y3.3 (OUT/IN)

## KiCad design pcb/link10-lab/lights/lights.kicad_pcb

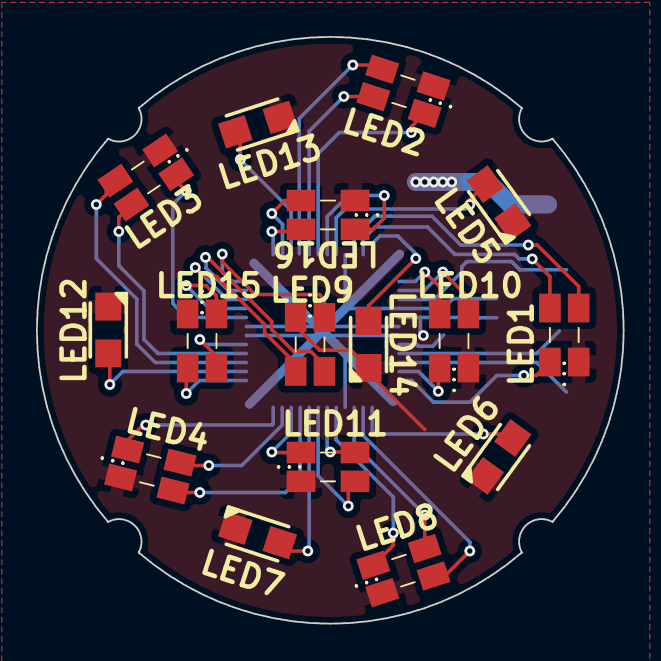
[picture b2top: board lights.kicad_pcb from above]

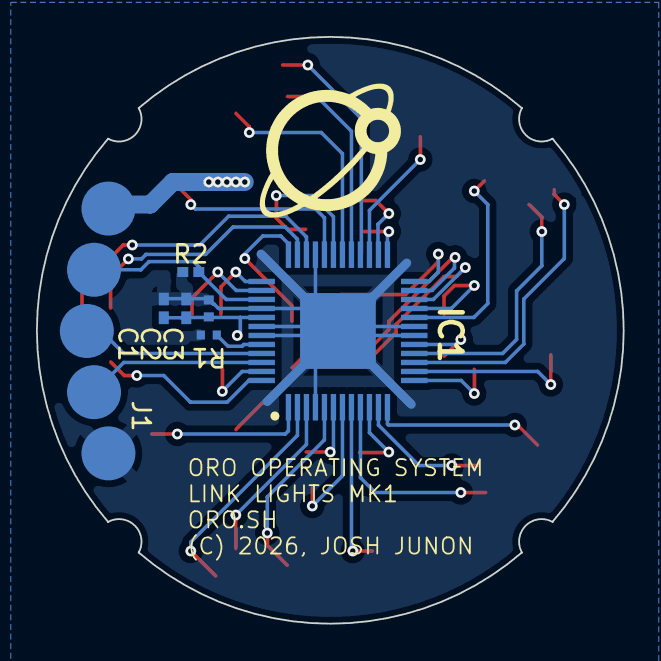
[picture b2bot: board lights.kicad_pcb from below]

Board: 2 copper layers, 32.6 x 32.6 mm, 23 parts (7 on the bottom side), 42 nets.

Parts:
C1: 1u; OP_0001R
C2: 0.1u; OP_0001Y
C3: 0.01u; OP_0000F
IC1: IS31FL3236A-TQLS4-TR; OP_0001Q
J1: Conn_01x05; Wire Jack 5p 18g
LED1, LED2, LED3, LED4, LED8, LED9, LED10, LED11, LED15, LED16: 150120M173000; OP_00006
LED5, LED6, LED7, LED12, LED13, LED14: CLM3C-WKW-CXAYA453; OP_00016
R1: 4.7K; OP_0001C
R2: 10K; OP_00021

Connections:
/+3V3: C1.1, C2.1, C3.1, IC1.41 (VCC), J1.1, LED1.2 (A_G), LED2.2 (A_G), LED3.2 (A_G), LED4.2 (A_G), LED5.1 (A), LED6.1 (A), LED7.1 (A), LED8.2 (A_G), LED9.2 (A_G), LED10.2 (A_G), LED11.2 (A_G), LED12.1 (A), LED13.1 (A), LED14.1 (A), LED15.2 (A_G), LED16.2 (A_G)
/EN: IC1.39 (SDB), J1.2, R2.2
/GND: C1.2, C2.2, C3.2, IC1.4 (GND_1), IC1.18 (GND_2), IC1.19 (GND_3), IC1.33 (GND_4), IC1.40 (AD), IC1.42 (GND_5), IC1.43 (GND_6), IC1.49 (EP), J1.5, R1.2, R2.1
/O1: IC1.47 (OUT1), LED10.1 (K_B)
/O2: IC1.48 (OUT2), LED1.1 (K_B)
/O3: IC1.1 (OUT3), LED6.2 (K)
/O4: IC1.2 (OUT4), LED8.3 (K_G)
/O5: IC1.3 (OUT5), LED8.4 (K_R)
/O6: IC1.5 (OUT6), LED8.1 (K_B)
/O7: IC1.6 (OUT7), LED11.4 (K_R)
/O8: IC1.7 (OUT8), LED11.3 (K_G)
/O9: IC1.8 (OUT9), LED7.2 (K)
/O10: IC1.9 (OUT10), LED4.3 (K_G)
/O11: IC1.10 (OUT11), LED11.1 (K_B)
/O12: IC1.11 (OUT12), LED4.4 (K_R)
/O13: IC1.12 (OUT13), LED4.1 (K_B)
/O14: IC1.13 (OUT14), LED15.3 (K_G)
/O15: IC1.14 (OUT15), LED12.2 (K)
/O16: IC1.15 (OUT16), LED3.3 (K_G)
/O17: IC1.16 (OUT17), LED3.4 (K_R)
/O18: IC1.17 (OUT18), LED15.4 (K_R)
/O19: IC1.20 (OUT19), LED3.1 (K_B)
/O20: IC1.21 (OUT20), LED15.1 (K_B)
/O21: IC1.22 (OUT21), LED9.3 (K_G)
/O22: IC1.23 (OUT22), LED9.4 (K_R)
/O23: IC1.24 (OUT23), LED9.1 (K_B)
/O24: IC1.25 (OUT24), LED16.4 (K_R)
/O25: IC1.26 (OUT25), LED16.3 (K_G)
/O26: IC1.27 (OUT26), LED13.2 (K)
/O27: IC1.28 (OUT27), LED2.3 (K_G)
/O28: IC1.29 (OUT28), LED2.4 (K_R)
/O29: IC1.30 (OUT29), LED2.1 (K_B)
/O30: IC1.31 (OUT30), LED16.1 (K_B)
/O31: IC1.32 (OUT31), LED5.2 (K)
/O32: IC1.34 (OUT32), LED1.3 (K_G)
/O33: IC1.35 (OUT33), LED1.4 (K_R)
/O34: IC1.36 (OUT34), LED14.2 (K)
/O35: IC1.37 (OUT35), LED10.4 (K_R)
/O36: IC1.38 (OUT36), LED10.3 (K_G)
/SCL: IC1.46 (SCL), J1.4
/SDA: IC1.45 (SDA), J1.3
unnamed: IC1.44 (R_EXT), R1.1

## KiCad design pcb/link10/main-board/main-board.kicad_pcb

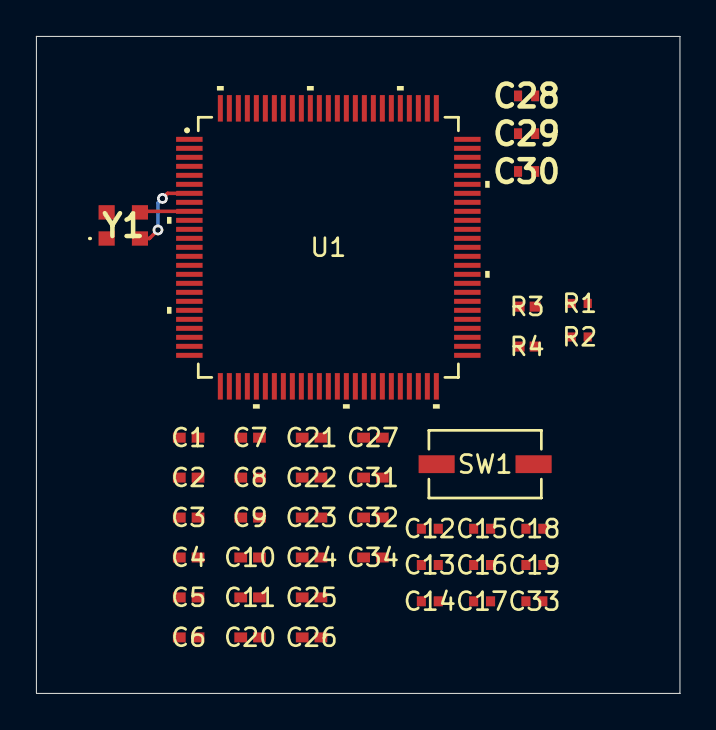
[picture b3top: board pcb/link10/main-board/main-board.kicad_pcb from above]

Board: 2 copper layers, 35.8 x 36.5 mm, 41 parts (0 on the bottom side), 10 nets.

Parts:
C1, C2, C3: 2.2u; CAP_MK105_V_TAY
C4, C5, C6, C7, C8, C9, C10, C11, C32, C34: 0.1u; CAP_MSAS1L-3_TAY
C12, C13, C14, C15, C16, C17, C18, C19, C33: 0.01u; CAP_0402_N_WAL
C20, C21, C22, C23, C24, C25, C26, C27, C31: 1u; cap_UMK105 CG080CV-F_TAY
C28, C29, C30: 4.7u; GRM15x
R1, R2: 4.7K; RES_CRCW_0402_VIS-L
R3, R4: 10K; STA_RMCF0402_STP
SW1: TL6400AF160QJ; SW_TL6400AF260QJ_EWI
U1: STM32F479VGT6; LQFP100_STM
Y1: ECS-2520SMV-240-FP-TR; ECS2520SMV240FPTR

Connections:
/Microcontroller/+3V3: C4.1, C5.1, C6.1, C7.1, C8.1, C9.1, C10.1, C11.1, C12.1, C13.1, C14.1, C15.1, C16.1, C17.1, C18.1, C19.1, C20.1, C21.1, C22.1, C23.1, C24.1, C25.1, C26.1, C27.1, C28.1, C29.1, C30.1, C31.2, C32.2, C33.2, R1.1, R2.1, R3.2, R4.2, U1.3 (VBAT), U1.8 (VDD), U1.17 (VREF+), U1.18 (VDDA), U1.24 (VDD), U1.45 (VDD), U1.55 (VDDDSI), U1.65 (VDDUSB), U1.77 (VDD), U1.100 (VDD), Y1.4 (VDD)
/Microcontroller/GND: C1.1, C2.1, C3.1, C4.2, C5.2, C6.2, C7.2, C8.2, C9.2, C10.2, C11.2, C12.2, C13.2, C14.2, C15.2, C16.2, C17.2, C18.2, C19.2, C20.2, C21.2, C22.2, C23.2, C24.2, C25.2, C26.2, C27.2, C28.2, C29.2, C30.2, C31.1, C32.1, C33.1, C34.2, SW1.2, U1.2 (VSS), U1.7 (VSS), U1.16 (VSSA), U1.23 (VSS), U1.44 (VSS), U1.59 (VSSDSI), U1.78 (VSS), Y1.2 (GND)
/Microcontroller/I2C1.SCL: R2.2, U1.98 (PB8)
/Microcontroller/I2C1.SDA: R1.2, U1.99 (PB9)
unnamed: C34.1, R4.1, SW1.1, U1.11 (NRST)
unnamed: U1.9 (PH0), Y1.3 (OUTPUT)
unnamed: C1.2, U1.43 (VCAP1)
unnamed: C2.2, U1.76 (VCAP2)
unnamed: C3.2, U1.56 (VCAPDSI), U1.62 (VDD12DSI)
unnamed: R3.1, Y1.1 (TRI-STATE)

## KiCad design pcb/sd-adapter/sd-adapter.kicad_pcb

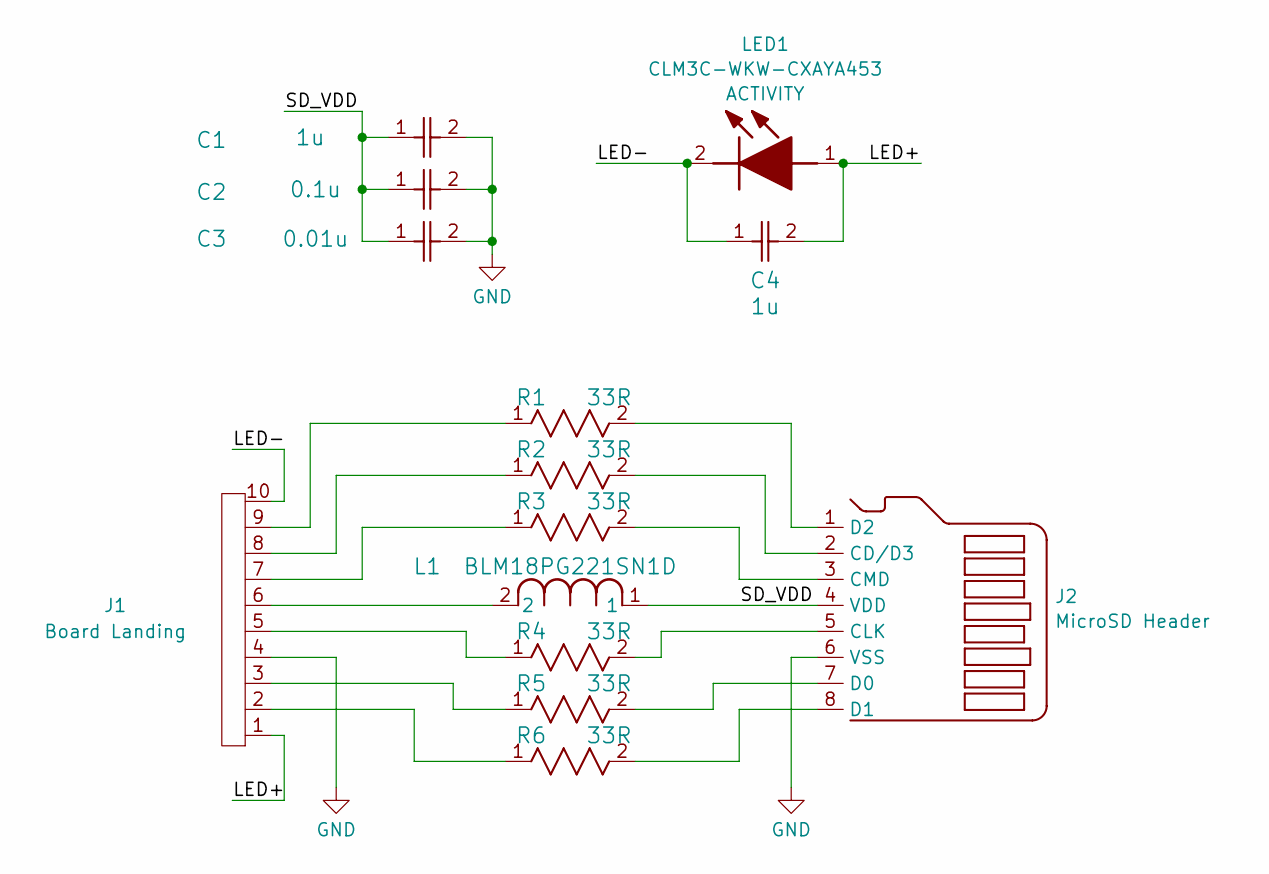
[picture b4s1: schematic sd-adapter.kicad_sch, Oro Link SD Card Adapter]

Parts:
C1, C4: 1u; cap_UMK105 CG080CV-F_TAY; DigiKey ID 587-3766-1-ND
C2: 0.1u; CAP_MSAS1L-3_TAY; DigiKey ID 587-MSAST1L3YB5104KFNA01CT-ND
C3: 0.01u; CAP_0402_N_WAL; Mouser ID 791-0402B103J160CT
J1: Board Landing; OroSDCardCouplingPadBoardSide
J2: MicroSD Header; SDCardOutlinePadsTop
L1: BLM18PG221SN1D; IND_BLM18_0603_MUR; DigiKey ID 490-5221-1-ND
LED1: CLM3C-WKW-CXAYA453; CLM3CWKWCXAYA453; Manufacturer_Part_Number CLM3C-WKW-CXAYA453; Mouser Part Number 941-CLM3CWKWCXAYA453
R1, R2, R3, R4, R5, R6: 33R; RES_0510_SUS; DigiKey ID RR05R33DCT-ND

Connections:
/LED+: C4.2, J1.1, LED1.1 (A); also elsewhere on the board
/LED-: C4.1, J1.10, LED1.2 (K); also elsewhere on the board
/SD_VDD: C1.1, C2.1, C3.1, J2.4 (VDD), L1.1
GND: C1.2, C2.2, C3.2, J1.4, J2.6 (VSS)
unnamed: J1.2, R6.1
unnamed: J1.3, R5.1
unnamed: J1.5, R4.1
unnamed: J1.6, L1.2
unnamed: J1.7, R3.1
unnamed: J1.8, R2.1
unnamed: J1.9, R1.1
unnamed: J2.2 (CD/D3), R2.2
unnamed: J2.5 (CLK), R4.2
unnamed: J2.3 (CMD), R3.2
unnamed: J2.7 (D0), R5.2
unnamed: J2.8 (D1), R6.2
unnamed: J2.1 (D2), R1.2

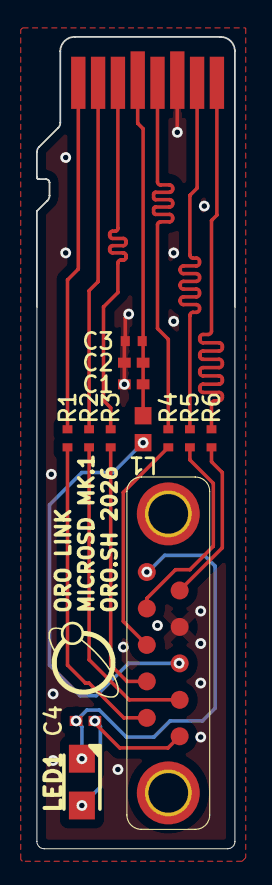
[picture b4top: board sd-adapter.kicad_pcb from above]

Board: 2 copper layers, 11.0 x 45.1 mm, 15 parts (1 on the bottom side), 17 nets.

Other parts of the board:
LED2: CLM3C-WKW-CXAYA453; CLM3CWKWCXAYA453

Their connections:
/LED+: LED2.1 (A); also elsewhere on the board
/LED-: LED2.2 (K); also elsewhere on the board

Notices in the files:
pcb/atx24-power/atx24_power.kicad_pcb:
Copyright (C) 2025, MPL-2.0
pcb/atx24-power/atx24_power.kicad_sch:
Copyright 2025, MPL 2.0
pcb/link10-lab/lights/lights.kicad_pcb:
Copyright 2023-2026, MPL 2.0
(C) 2026, JOSH JUNON
